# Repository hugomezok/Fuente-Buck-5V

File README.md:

# Fuente-Buck-5V

Proyecto para la materia "Electrónica de Potencia" de la UTN-FRBA.  
En el contexto de aplicaciones de alta frecuencia, se desarolló una fuente reductora tipo Buck con salida de 5 volts, basada en el CI LM2596.

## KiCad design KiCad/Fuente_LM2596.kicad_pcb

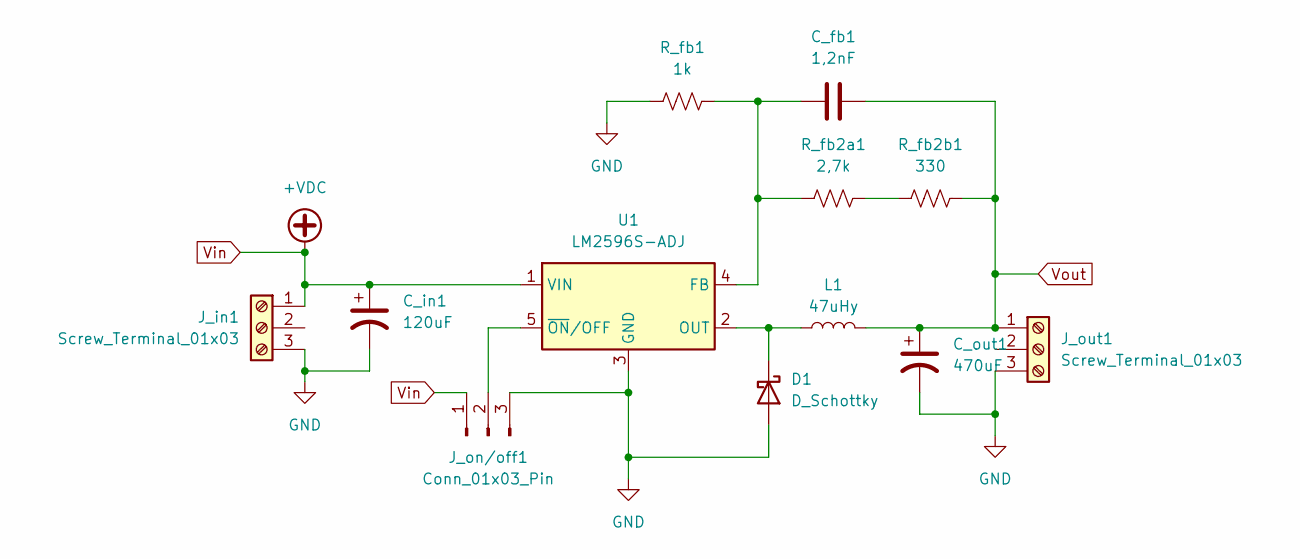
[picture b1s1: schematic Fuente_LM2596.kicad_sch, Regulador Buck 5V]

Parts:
C_fb1: 1,2nF; C_Disc_D3.0mm_W2.0mm_P2.50mm
C_in1: 120uF; CP_Radial_D13.0mm_P5.00mm
C_out1: 470uF; CP_Radial_D13.0mm_P5.00mm
D1: D_Schottky; D_5W_P12.70mm_Horizontal
J_in1: Screw_Terminal_01x03; TerminalBlock_TE_282834-3_1x03_P2.54mm_Horizontal
J_on/off1: Conn_01x03_Pin; PinSocket_1x03_P2.54mm_Vertical
J_out1: Screw_Terminal_01x03; TerminalBlock_TE_282834-3_1x03_P2.54mm_Horizontal
L1: 47uHy; L_Coilcraft_MSS1210-XXX
R_fb1: 1k; R_Axial_DIN0309_L9.0mm_D3.2mm_P12.70mm_Horizontal
R_fb2a1: 2,7k; R_Axial_DIN0309_L9.0mm_D3.2mm_P12.70mm_Horizontal
R_fb2b1: 330; R_Axial_DIN0414_L11.9mm_D4.5mm_P5.08mm_Vertical
U1: LM2596S-ADJ; TO-263-5_TabPin3

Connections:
GND: C_in1.2, C_out1.2, D1.2 (A), J_in1.3, J_on/off1.3, J_out1.3, R_fb1.1, U1.3 (GND)
unnamed: D1.1 (K), L1.1, U1.2 (OUT)
unnamed: J_on/off1.2, U1.5 (~ON/OFF)
unnamed: R_fb2a1.2, R_fb2b1.1
unnamed: C_fb1.1, R_fb1.2, R_fb2a1.1, U1.4 (FB)
Vin: C_in1.1, J_in1.1, J_on/off1.1, U1.1 (VIN)
Vout: C_fb1.2, C_out1.1, J_out1.1, L1.2, R_fb2b1.2

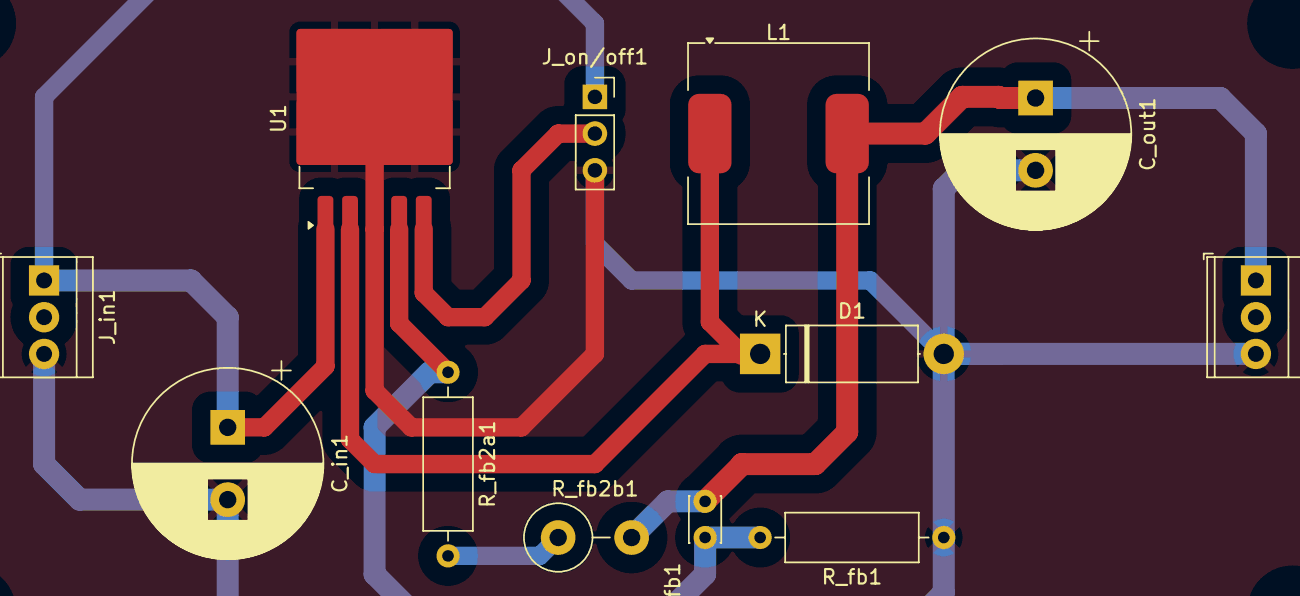
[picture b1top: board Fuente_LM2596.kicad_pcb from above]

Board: 2 copper layers, 12 parts (0 on the bottom side), 7 nets.

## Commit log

2025-04-02 Commit de la documentación del proyecto
